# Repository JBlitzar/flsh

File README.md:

# flsh

A flashlight with the brightness of 83 iphones.

Some features:
 - 9x OSRAM GW PUSTA1.PM-PBQB-XX52-1-1050-R18 for ~5000 lm nominal.
 - XL6006 driver board designed to boost a 2x21700 pack up to the required 28v​@1.1A

I made this because I thought it would be pretty cool. Also I got to think about designing power circuitry. I looked at a lot of different ICs before settling on the XL6006. In the end, TI and Analog both were beaten out by Shanghai Xinlong Semiconductor Technology Co., Ltd, so there you go! While the XL6006 gets a bad rap on cheap aliexpress boost boards, the chip itself will work fine if you have a good inductor etc. And it only requires like five passives to work! I evaluated a lot of different designs, see [planning](planning/). 

In terms of the LEDs, I pretty much went on to LCSC and clicked "sort high to low" on lumens. But really, I thought this was more reasonable than most CoB solutions. 

You might be wondering why they are in series. This is to prevent thermal runaway, where one LED uses slightly more current, which causes it to get hotter, which causes it to hog current slightly more, etc in a positive feedback loop. You can use ballast resistors. I just wired them in series and accepted the steep boost ratio.

PWM dimming? hahaha you can source and solder a different sense resistor to get a different brightness.

## How to use?

2x21700 to `VIN` / `GND` on the boost board, then `LED+` / `LED-` on the boost board to `VCC` / `GND` on the emitter board.

As you can tell, this is, for the moment, mostly the bones of a flashlight (ie the PCBs) rather than an actual assembly. 

## Schematics

[Interactive unified viewer](https://hurt-xi.vercel.app/?repo=https%3A%2F%2Fgithub.com%2Fjblitzar%2Fflsh)

### flsh boost

[View on KiCanvas](https://kicanvas.org/?repo=https%3A%2F%2Fgithub.com%2FJBlitzar%2Fflsh%2Ftree%2Fmain%2FPCB%2Fflsh)

### flsh led

[View on KiCanvas](https://kicanvas.org/?repo=https%3A%2F%2Fgithub.com%2FJBlitzar%2Fflsh%2Ftree%2Fmain%2FPCB%2Fflsh)

## PCBs

### flsh boost

[View on KiCanvas](https://kicanvas.org/?repo=https%3A%2F%2Fgithub.com%2FJBlitzar%2Fflsh%2Ftree%2Fmain%2FPCB%2Fflsh) | [View iBOM](https://htmlpreview.github.io/?https://github.com/JBlitzar/flsh/blob/main/PCB/flsh/bom/ibom.html) (or open `PCB/flsh/bom/ibom.html` locally)

<table>
  <tr>
    <td width="50%"></td>
    <td width="50%"></td>
  </tr>
</table>

### flsh led

[View on KiCanvas](https://kicanvas.org/?repo=https%3A%2F%2Fgithub.com%2FJBlitzar%2Fflsh%2Ftree%2Fmain%2FPCB%2Fflsh)

<table>
  <tr>
    <td width="50%"></td>
    <td width="50%"></td>
  </tr>
</table>

## About cost

This is a ballpark, YMMV based on sourcing, promotions, discounts

## Overall BOM

|Item            |Link                                              |Extended Cost|Notes                                      |
|----------------|--------------------------------------------------|-------------|-------------------------------------------|
|10x LEDs (MOQ)  |https://www.lcsc.com/product-detail/C46046287.html|17.15        |                                           |
|LED PCB         |N/A                                               |2.44         |                                           |
|Boost components|N/A                                               |18           |See fabrication BOM in README for C-numbers|
|LCSC shipping   |N/A                                               |8            |                                           |
|JLC shipping    |N/A                                               |3.3          |                                           |
|                |                                                  |             |                                           |
|Total           |                                                  |48.89        |                                           |

## Fabrication BOMs

### flsh boost

| Designator | Footprint | Quantity | Value | LCSC Part # |
| --- | --- | --- | --- | --- |
| C1 | C_2220_5750Metric | 1 | 47uF 35V | C27840590 |
| C2 | CAP-SMD_BD10.0-L10.3-W10.3-FD | 1 | 100uF 63V | C53120969 |
| C3, C4 | C_1206_3216Metric | 2 | 1uF | C13832 |
| D1 | D_SMA | 1 | SS38 | C64999 |
| DZ1 | D_SOD-123F | 1 | ZENER (BZT52C39, 39V) | C49023525 |
| L1 | IND-SMD_L13.8-W12.6_H6.5 | 1 | YSPI1365-470M (47uH) | C497913 |
| R1 | R_1206_3216Metric | 1 | 2k | C133543 |
| RS1 | R_2512_6332Metric | 1 | JER2512F2R220 (0.22R) | C49164922 |
| U2 | TO-263-5_L10.2-W9.9-P1.70-LS14.4-TL | 1 | XL6006E1 | C73346 |

### flsh led

| Designator | Footprint | Quantity | Value | LCSC Part # |
| --- | --- | --- | --- | --- |
| LED1, LED2, LED3, LED4, LED5, LED6, LED7, LED8, LED9 | LED-SMD_3P-L3.7-W3.7_GW-PUSTA1.PM-NAPD-XX510-1-1050-R18 | 9 | GW PUSTA1.PM-PBQB-XX52-1-1050-R18 | C46046287 |

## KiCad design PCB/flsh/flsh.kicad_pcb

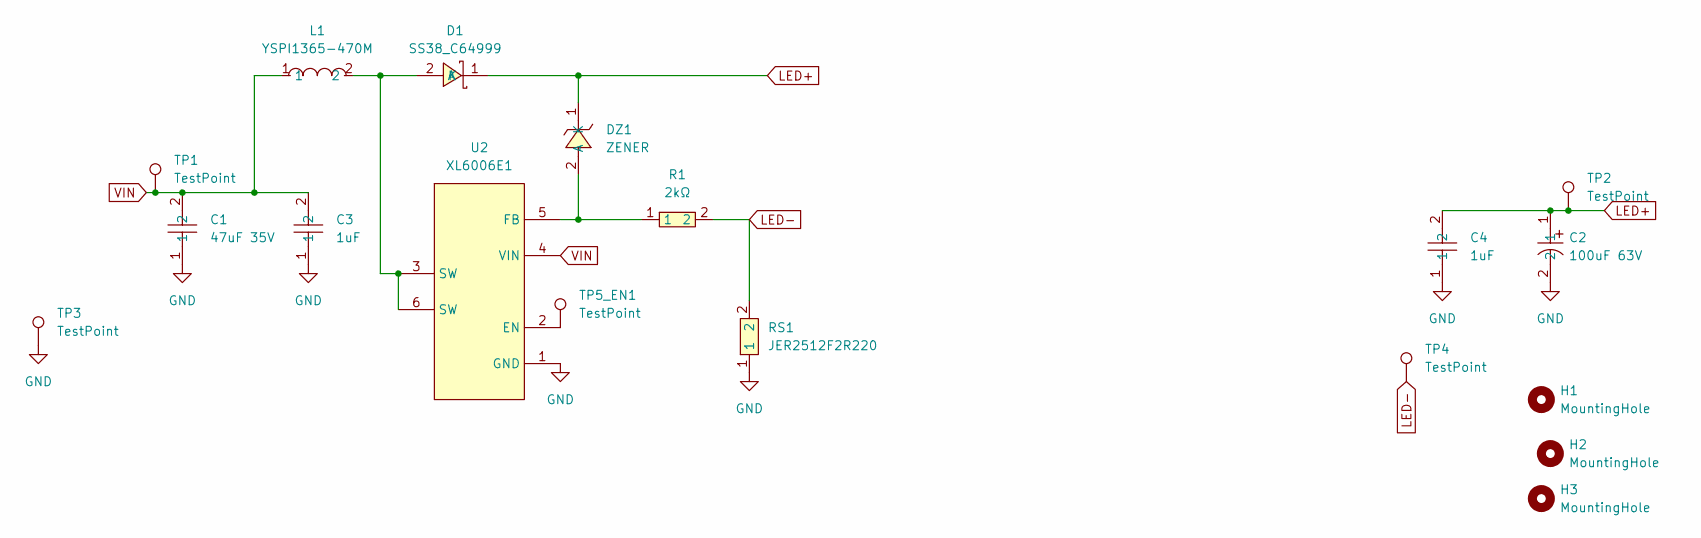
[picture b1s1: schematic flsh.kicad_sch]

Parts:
C1: 47uF 35V; C_2220_5750Metric; MPN KTJ350B476M55BFT00; LCSC Part C27840590
C2: 100uF 63V; CAP-SMD_BD10.0-L10.3-W10.3-FD; MPN MA80V100M10X12; LCSC Part C53120969
C3, C4: 1uF; C_1206_3216Metric; MPN CL31B105KCHNNNE; LCSC Part C13832
D1: SS38_C64999; D_SMA; MPN SS38; LCSC Part C64999
DZ1: ZENER; D_SOD-123F; MPN BZT52C39 WT; LCSC Part C49023525
H1, H2, H3: MountingHole; MountingHole_3.2mm_M3
L1: YSPI1365-470M; IND-SMD_L13.8-W12.6_H6.5; MPN YSPI1365-470M; LCSC Part C497913
R1: 2kΩ; R_1206_3216Metric; MPN RC1206FR-072KL; LCSC Part C133543
RS1: JER2512F2R220; R_2512_6332Metric; MPN JER2512F2R220; LCSC Part C49164922
TP1, TP2, TP3, TP4, TP5_EN1: TestPoint; TestPoint_Pad_D4.0mm
U2: XL6006E1; TO-263-5_L10.2-W9.9-P1.70-LS14.4-TL; MPN XL6006E1; LCSC Part C73346

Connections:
GND: C1.1, C2.2, C3.1, C4.1, RS1.1, TP3.1 (1_1), U2.1 (GND)
LED+: C2.1, C4.2, D1.1 (K), DZ1.1 (K), TP2.1 (1_1)
LED-: R1.2, RS1.2, TP4.1 (1_1)
unnamed: D1.2 (A), L1.2, U2.3 (SW), U2.6 (SW)
unnamed: DZ1.2 (A), R1.1, U2.5 (FB)
unnamed: TP5_EN1.1 (1_1), U2.2 (EN)
VIN: C1.2, C3.2, L1.1, TP1.1 (1_1), U2.4 (VIN)

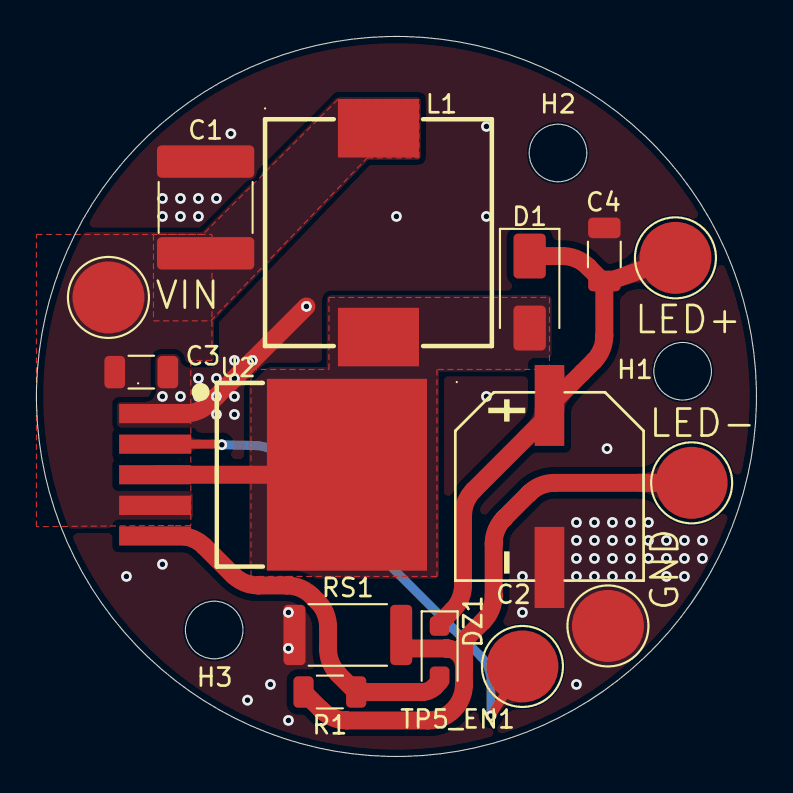
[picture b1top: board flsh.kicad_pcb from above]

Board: 2 copper layers, 40.0 x 40.0 mm, 19 parts (1 on the bottom side), 7 nets.

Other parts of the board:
kobee-studio-6ADE59CA: Kobee Studio; kobee-studio-6ADE59CA

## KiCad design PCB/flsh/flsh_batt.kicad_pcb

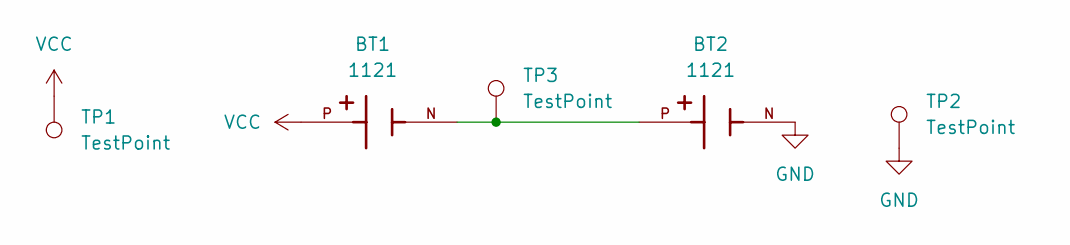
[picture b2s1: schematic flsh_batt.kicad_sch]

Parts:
BT1, BT2: 1121; BAT_1121; PARTREV A
TP1, TP2, TP3: TestPoint; TestPoint_Pad_D4.0mm

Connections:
GND: BT2.N, TP2.1 (1_1)
unnamed: BT1.N, BT2.P, TP3.1 (1_1)
VCC: BT1.P, TP1.1 (1_1)

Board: 2 copper layers, 5 parts (0 on the bottom side), 3 nets, no tracks yet.

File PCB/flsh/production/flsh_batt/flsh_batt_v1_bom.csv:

Designator,Footprint,Quantity,Value,LCSC Part #
"BT1, BT2",BAT_1121,2,1121,
"TP1, TP2, TP3",TestPoint_Pad_D4.0mm,3,TestPoint,

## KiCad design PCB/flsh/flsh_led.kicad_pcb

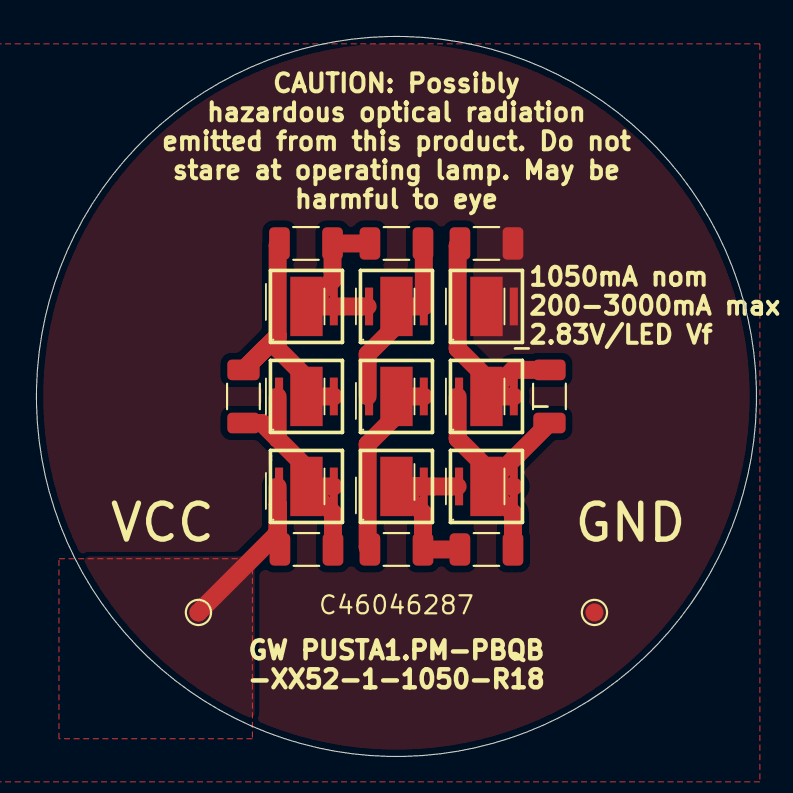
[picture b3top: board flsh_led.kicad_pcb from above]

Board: 2 copper layers, 40.0 x 40.0 mm, 19 parts (0 on the bottom side), 10 nets.

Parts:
C1, C2, C3, C4, C5, C6, C7, C8: C_US; C_1206_3216Metric
LED1, LED2, LED3, LED4, LED5, LED6, LED7, LED8, LED9: GW PUSTA1.PM-PBQB-XX52-1-1050-R18; LED-SMD_3P-L3.7-W3.7_GW-PUSTA1.PM-NAPD-XX510-1-1050-R18
TP1, TP2: TestPoint; TestPoint_Pad_D1.0mm

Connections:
GND: C4.1, LED9.2 (C), LED9.3 (C), TP2.1 (1_1)
LED_VCC: C1.2, LED6.1 (A), TP1.1 (1_1)
unnamed: C2.2, C5.1, LED1.1 (A), LED7.2 (C), LED7.3 (C)
unnamed: C2.1, C6.2, LED1.2 (C), LED1.3 (C), LED2.1 (A)
unnamed: C6.1, LED2.2 (C), LED2.3 (C), LED3.1 (A)
unnamed: C7.2, LED3.2 (C), LED3.3 (C), LED4.1 (A)
unnamed: C3.2, C7.1, LED4.2 (C), LED4.3 (C), LED5.1 (A)
unnamed: C1.1, C5.2, LED6.2 (C), LED6.3 (C), LED7.1 (A)
unnamed: C3.1, C8.2, LED5.2 (C), LED5.3 (C), LED8.1 (A)
unnamed: C4.2, C8.1, LED8.2 (C), LED8.3 (C), LED9.1 (A)
